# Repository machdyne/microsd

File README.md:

# High-Speed MicroSD Pmod&trade; compatible module

This is a 12-pin Pmod™ compatible module with a MicroSD slot and optional 3.3V<->1.8V level translation.

This repo contains pinouts, schematics and PCB layouts.

Find more information on the [MicroSD product page](https://machdyne.com/product/microsd-pmod/).

## Pinout

| Pin | Signal|
| --- | ----- |
| 1 | SD\_SS |
| 2 | SD\_MOSI |
| 3 | SD\_MISO |
| 4 | SD\_SCK |
| 5 | GND |
| 6 | 3V3 |
| 7 | SD\_DAT1 |
| 8 | SD\_DAT2 |
| 9 | SD\_CD |
| 10 | SD\_VSEL18 |
| 11 | GND |
| 12 | 3V3 |

Note: 1.8V signals are used when SD\_VSEL18 is high, or 3.3V when low (default).

Note: When SD\_CD is asserted high for >100ms, power is shut off to the MicroSD card, allowing reset. All other signals should be held low during reset.

## Revisions

| Revision | Stackup | Notes |
| -------- | ------- | ----- |
| V0 | Aisler 4L | Initial prototype |

## License

The contents of this repo are released under the [Lone Dynamics Open License](LICENSE.md).

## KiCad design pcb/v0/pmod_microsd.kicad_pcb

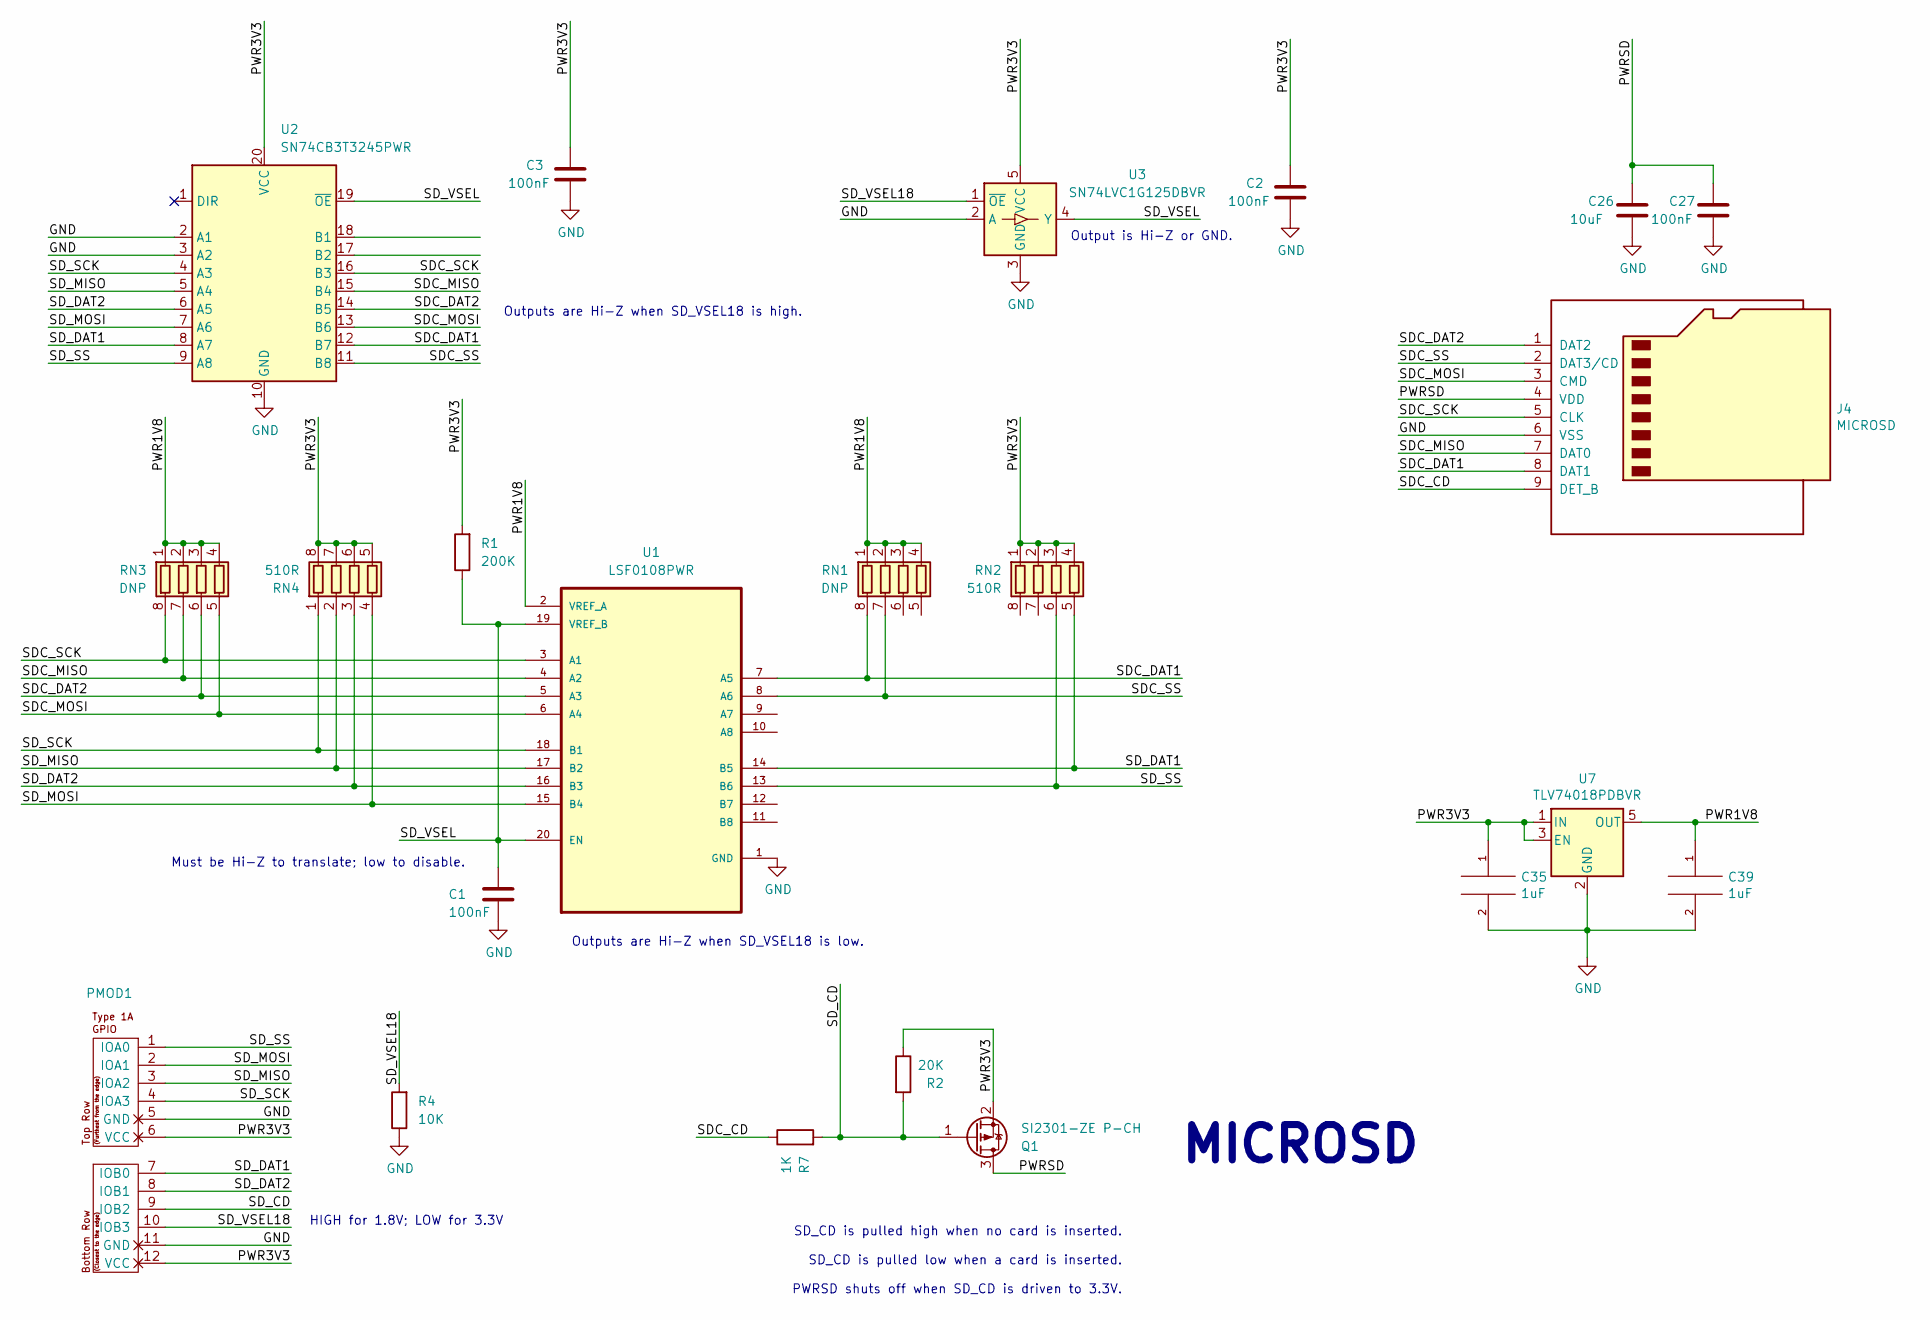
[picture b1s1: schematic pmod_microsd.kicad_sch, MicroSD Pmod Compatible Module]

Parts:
C1, C2, C3, C27: 100nF; C_0402_1005Metric
C26: 10uF; C_0402_1005Metric
C35, C39: 1uF; C_0402_1005Metric
J4: MICROSD; SDCARD
PMOD1: PMOD-Device-x2-Type-1A-GPIO; pmod_pin_array_6x2
Q1: SI2301-ZE P-CH; SOT-23
R1: 200K; R_0402_1005Metric
R2: 20K; R_0402_1005Metric
R4: 10K; R_0402_1005Metric
R7: 1K; R_0402_1005Metric
RN1, RN3: DNP; R_Array_Convex_4x0402
RN2, RN4: 510R; R_Array_Convex_4x0402
U1: LSF0108PWR; TSSOP-20_4.4x6.5mm_P0.65mm
U2: SN74CB3T3245PWR; TSSOP-20_4.4x6.5mm_P0.65mm
U3: SN74LVC1G125DBVR; SOT-23-5
U7: TLV74018PDBVR; SOT-23-5

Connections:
/PWR1V8: C39.1, RN1.1 (R1.1), RN1.2 (R2.1), RN1.3 (R3.1), RN1.4 (R4.1), RN3.1 (R1.1), RN3.2 (R2.1), RN3.3 (R3.1), RN3.4 (R4.1), U1.2 (VREF_A), U7.5 (OUT)
/PWR3V3: C2.1, C3.1, C35.1, PMOD1.6 (VCC), PMOD1.12 (VCC), Q1.2 (S), R1.2, R2.1, RN2.1 (R1.1), RN2.2 (R2.1), RN2.3 (R3.1), RN2.4 (R4.1), RN4.5 (R4.2), RN4.6 (R3.2), RN4.7 (R2.2), RN4.8 (R1.2), U2.20 (VCC), U3.5 (VCC), U7.1 (IN), U7.3 (EN)
/PWRSD: C26.1, C27.1, J4.4 (VDD), Q1.3 (D)
/SDC_CD: J4.9 (DET_B), R7.1
/SDC_DAT1: J4.8 (DAT1), RN1.8 (R1.2), U1.7 (A5), U2.12 (B7)
/SDC_DAT2: J4.1 (DAT2), RN3.6 (R3.2), U1.5 (A3), U2.14 (B5)
/SDC_MISO: J4.7 (DAT0), RN3.7 (R2.2), U1.4 (A2), U2.15 (B4)
/SDC_MOSI: J4.3 (CMD), RN3.5 (R4.2), U1.6 (A4), U2.13 (B6)
/SDC_SCK: J4.5 (CLK), RN3.8 (R1.2), U1.3 (A1), U2.16 (B3)
/SDC_SS: J4.2 (DAT3/CD), RN1.7 (R2.2), U1.8 (A6), U2.11 (B8)
/SD_CD: PMOD1.9 (IOB2), Q1.1 (G), R2.2, R7.2
/SD_DAT1: PMOD1.7 (IOB0), RN2.5 (R4.2), U1.14 (B5), U2.8 (A7)
/SD_DAT2: PMOD1.8 (IOB1), RN4.3 (R3.1), U1.16 (B3), U2.6 (A5)
/SD_MISO: PMOD1.3 (IOA2), RN4.2 (R2.1), U1.17 (B2), U2.5 (A4)
/SD_MOSI: PMOD1.2 (IOA1), RN4.4 (R4.1), U1.15 (B4), U2.7 (A6)
/SD_SCK: PMOD1.4 (IOA3), RN4.1 (R1.1), U1.18 (B1), U2.4 (A3)
/SD_SS: PMOD1.1 (IOA0), RN2.6 (R3.2), U1.13 (B6), U2.9 (A8)
/SD_VSEL: C1.1, R1.1, U1.19 (VREF_B), U1.20 (EN), U2.19 (~OE), U3.4 (Y)
/SD_VSEL18: PMOD1.10 (IOB3), R4.2, U3.1 (~OE)
GND: C1.2, C2.2, C3.2, C26.2, C27.2, C35.2, C39.2, J4.6 (VSS), PMOD1.5 (GND), PMOD1.11 (GND), R4.1, U1.1 (GND), U2.2 (A1), U2.3 (A2), U2.10 (GND), U3.2 (A), U3.3 (GND), U7.2 (GND)

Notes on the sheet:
SD_CD is pulled high when no card is inserted. SD_CD is pulled low when a card is inserted. PWRSD shuts off when SD_CD is driven to 3.3V.
Outputs are Hi-Z when SD_VSEL18 is high.
Must be Hi-Z to translate; low to disable.
Outputs are Hi-Z when SD_VSEL18 is low.
Output is Hi-Z or GND.
MICROSD
HIGH for 1.8V; LOW for 3.3V

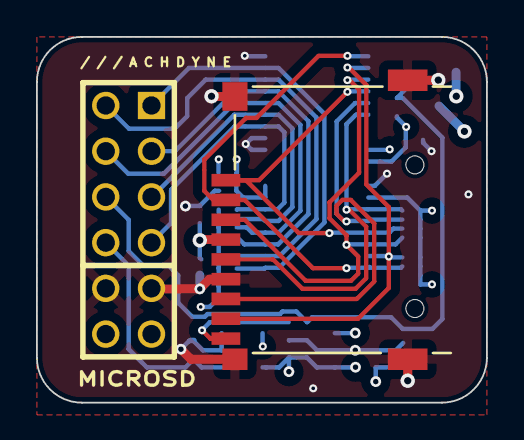
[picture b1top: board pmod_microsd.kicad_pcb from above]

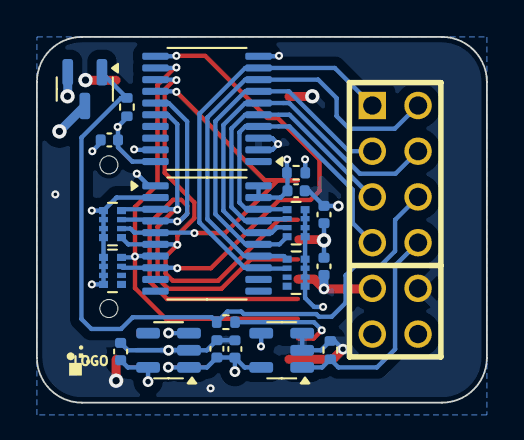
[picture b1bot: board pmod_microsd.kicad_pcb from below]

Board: 4 copper layers, 25.0 x 20.3 mm, 22 parts (20 on the bottom side), 20 nets.

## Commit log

2024-10-11 add render
2024-10-11 update render
2024-10-12 add hardware reset
2024-10-23 update values
2025-02-06 update readme & schematics

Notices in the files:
pcb/v0/pmod_microsd.kicad_sch:
Copyright © 2024 Lone Dynamics Corporation
